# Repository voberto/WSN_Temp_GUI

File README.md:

# WSN_Temp_GUI
ESP8266/ESP32 Temperature Measurement Wireless Sensor Node (+DS18B20) with Graphical User Interface program.

### 1 - Overview

This project comprises a minimal HW/SW design for the ESP8266 Node MCU board to send periodic measurements from the DS18B20 digital temperature sensor to a Python-based graphical user interface program through 'mosquitto' MQTT broker. A general block diagram of the included parts is depicted below.

### 2 - Contents

- '/wsn' -> hardware (Eagle schematic and board files) and software (Arduino files) related to the Node MCU board.

- '/client' -> all the software for the GUI program.

### 3 -  Components

NOTE: change the IP address, SSID and password in the 'wsn_v001_main.ino' (lines 49, 50 and 52) and 'gui_vars.py' (line 21) files to match your broker's IP and desired Wifi router credentials before running this project.

#### 3.1 - Broker

The MQTT message broker client called 'mosquito' (https://mosquitto.org/) was used in a virtual machine (VirtualBox) with Ubuntu 18.04 LTS in this project. To install required application and libraries:
```
$ sudo apt-add-repository ppa:mosquitto-dev/mosquitto-ppa
$ sudo apt-get update
$ sudo apt-get install mosquitto
$ sudo apt-get install mosquitto-clients
```

After installation, mosquitto is enabled as a service and its status can be checked with:
```
$ service mosquitto status
```

Incoming messages can be checked by subscribing to the desired channel, such as:
```
$ mosquitto_sub -h <BROKER_IP> -t <TOPIC>
```

#### 3.2 - Wireless Sensor Node (WSN)

The temperature measurement system is provided by a ESP8266 NodeMCU board and a DS18B20 digital IC thermometer. The software was developed using the Arduino 1.8.9 IDE and the following libraries are needed:

- ESP8266 Arduino Core (http://arduino.esp8266.com/Arduino/versions/2.0.0/doc/installing.html),

- WiFiManager (tzapu),

- PubSubClient (Nick O' Leary),

- OneWire (several authors) and

- DallasTemperature (Tim Burton, etc.).

If desired, a virtual WiFi hotpost can be created with 'create_ap' (https://github.com/oblique/create_ap) in Linux to hide the router's credentials while developing. To start the bridged WiFi interface for this project:
```
$ sudo create_ap <INTERFACE> <INTERFACE> <NEW_SSID> <NEW_PASSWORD>
```

#### 3.3 - Application with GUI

As the main user interface, a Python-based application (gui_main.py) was designed to receive temperature measurements and plot them in (almost) real time. The program also logs all data in a csv file. The main libraries for this project are:

 - Kivy (GUI framework) and
 
 - Matplotlib (chart plotting).
 
For better management of the development process (sandboxing of specific Python libraries), the GUI program was developed inside a virtual environment using the 'venv' package. All required libraries are depicted in the 'libs.txt' file. To create and initialize a new dev environment, create a separate folder and run the following commands:
```
$ python3 -m venv <DEV_PATH>      ## Create the environment
$ source <DEV_PATH>/bin/activate  ## Enable the environment
```
To install the libraries used in the GUI program, move the "libs.txt" file to the dev path and run:
```
$ pip install -r libs.txt
```

After that, don't forget to add all Python library paths to the .gitignore file. Finally, copy all the /src files to the dev path, run the 'gui_main.py' script and enjoy!

#### 3.4 - Example usage

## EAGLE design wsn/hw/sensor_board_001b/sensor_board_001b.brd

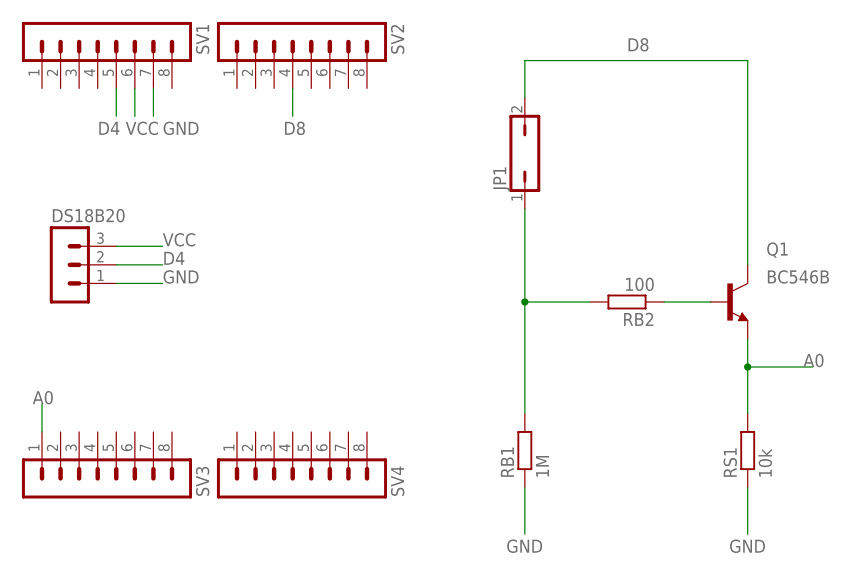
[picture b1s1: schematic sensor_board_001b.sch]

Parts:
DS18B20: MA03-1
JP1: JP1Q; JP1
Q1: BC546B; TO92-EBC
RB1: 1M; 0204/5
RB2: 100; 0204V
RS1: 10k; 0204/7
SV1, SV2, SV3, SV4: MA08-1

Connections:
A0: Q1.E, RS1.2, SV3.1
D4: DS18B20.2, SV1.5
D8: JP1.2, Q1.C, SV2.4
GND: DS18B20.1, RB1.1, RS1.1, SV1.7
unnamed: Q1.B, RB2.1
unnamed: JP1.1, RB1.2, RB2.2
VCC: DS18B20.3, SV1.6

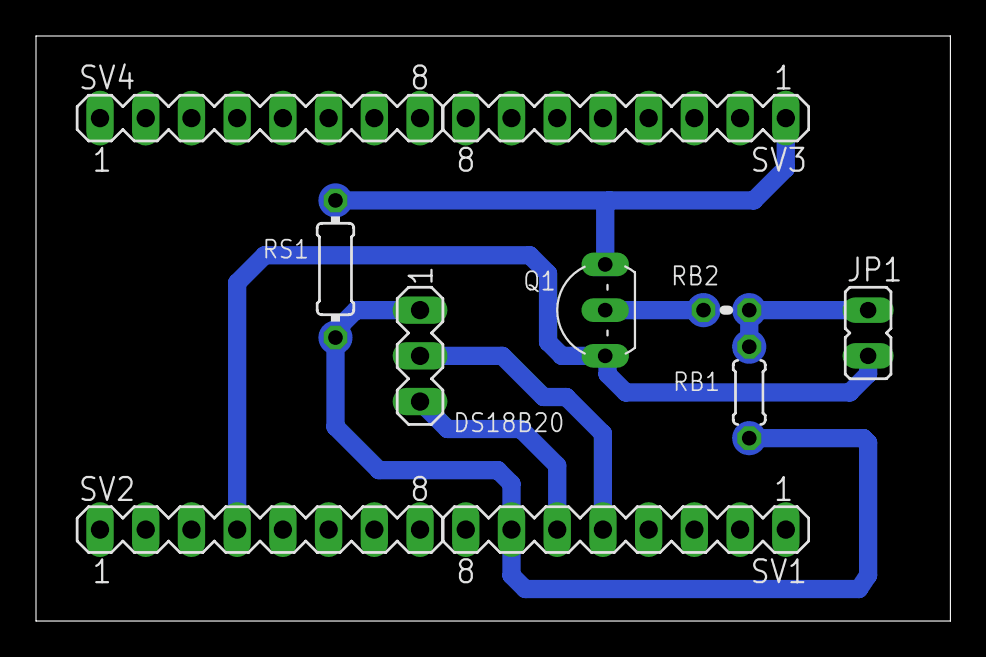
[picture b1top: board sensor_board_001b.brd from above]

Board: 2 copper layers, 50.8 x 32.5 mm, 10 parts (0 on the bottom side), 7 nets.

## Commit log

2019-08-07 First commit with code.
2019-08-08 Figure wsn_temp_gui_diagram001.png added.
2019-08-09 Example usage gif added.
